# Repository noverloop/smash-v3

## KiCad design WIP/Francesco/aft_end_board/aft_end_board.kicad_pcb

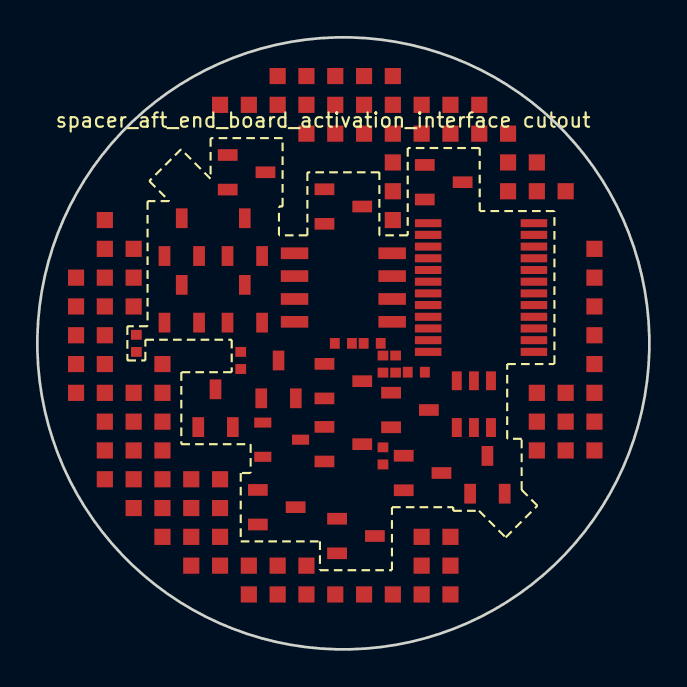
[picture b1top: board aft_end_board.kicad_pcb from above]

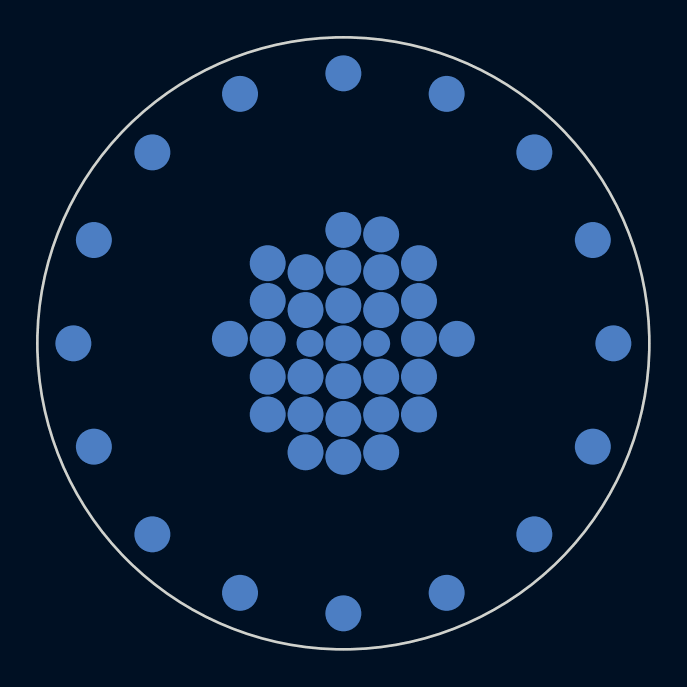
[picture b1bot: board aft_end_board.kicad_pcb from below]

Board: 14 copper layers, 34.0 x 34.0 mm, 77 parts (48 on the bottom side), 71 nets, no tracks yet.

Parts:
C_CAN_GW: C0402 X7R 100nF; Capacitor_SMD_C_0402_1005Metric
J_aft_end_board_spacer_aft_end_board_activation_interface: LGA_lands; J_aft_end_board_spacer_aft_end_board_activation_interface
P_ACT_WIRE_0: P_ACT_WIRE_0; Pogo_Pad_D2.0mm
P_ACT_WIRE_1: P_ACT_WIRE_1; Pogo_Pad_D2.0mm
P_ACT_WIRE_2: P_ACT_WIRE_2; Pogo_Pad_D2.0mm
P_ACT_WIRE_3: P_ACT_WIRE_3; Pogo_Pad_D2.0mm
P_ACT_WIRE_4: P_ACT_WIRE_4; Pogo_Pad_D2.0mm
P_ACT_WIRE_5: P_ACT_WIRE_5; Pogo_Pad_D2.0mm
P_ACT_WIRE_6: P_ACT_WIRE_6; Pogo_Pad_D2.0mm
P_ACT_WIRE_7: P_ACT_WIRE_7; Pogo_Pad_D2.0mm
P_ACT_WIRE_8: P_ACT_WIRE_8; Pogo_Pad_D2.0mm
P_ACT_WIRE_9: P_ACT_WIRE_9; Pogo_Pad_D2.0mm
P_ACT_WIRE_10: P_ACT_WIRE_10; Pogo_Pad_D2.0mm
P_ACT_WIRE_11: P_ACT_WIRE_11; Pogo_Pad_D2.0mm
P_ACT_WIRE_12: P_ACT_WIRE_12; Pogo_Pad_D2.0mm
P_ACT_WIRE_13: P_ACT_WIRE_13; Pogo_Pad_D2.0mm
P_ACT_WIRE_14: P_ACT_WIRE_14; Pogo_Pad_D2.0mm
P_ACT_WIRE_15: P_ACT_WIRE_15; Pogo_Pad_D2.0mm
P_FIRE_COMMON: P_FIRE_COMMON; Pogo_Pad_D2.0mm
Q_FIRE_ARM: DMP6110SVT-7; SOT95P280X100-6N
Q_FIRE_ARM_LS: BSS138LT1G; SOT96P237X111-3N
Q_FIRE_N0, Q_FIRE_N1, Q_FIRE_N2, Q_FIRE_N3, Q_FIRE_N4, Q_FIRE_N5, Q_FIRE_N6, Q_FIRE_N7, Q_FIRE_N8, Q_FIRE_N9, Q_FIRE_N10, Q_FIRE_N11, Q_FIRE_N12, Q_FIRE_N13, Q_FIRE_N14, Q_FIRE_N15: DMN6075SQ-7; SOT96P240X110-3N
R_EXT_CAN_TERM: CRCW0402 120 1% e3; Resistor_SMD_R_0402_1005Metric
R_FIRE_ARM_H: CRCW0402 100k 1% e3; Resistor_SMD_R_0402_1005Metric
R_FIRE_ARM_L: CRCW0402 100k 1% e3; Resistor_SMD_R_0402_1005Metric
R_FIRE_BLEED: CRCW0402 100k 1% e3; Resistor_SMD_R_0402_1005Metric
R_FIRE_MON1: CRCW0402 100k 1% e3; Resistor_SMD_R_0402_1005Metric
R_FIRE_MON2: CRCW0402 11k 1% e3; Resistor_SMD_R_0402_1005Metric
R_JUMP_PAD: CRCW0402 10k 1% e3; Resistor_SMD_R_0402_1005Metric
TP_ACT_CONFIRM: TP_ACT_CONFIRM; Pogo_Pad_D2.0mm
TP_ACT_MOTOR1: TP_ACT_MOTOR1; Pogo_Pad_D2.0mm
TP_ACT_MOTOR2: TP_ACT_MOTOR2; Pogo_Pad_D2.0mm
TP_ACT_MOTOR3: TP_ACT_MOTOR3; Pogo_Pad_D2.0mm
TP_ACT_MOTOR4: TP_ACT_MOTOR4; Pogo_Pad_D2.0mm
TP_ACT_SET: TP_ACT_SET; Pogo_Pad_D2.0mm
TP_BAT_PROT: TP_BAT_PROT; Pogo_Pad_D2.0mm
TP_BAT_RAW: TP_BAT_RAW; Pogo_Pad_D2.0mm
TP_BOOT0: TP_BOOT0; Pogo_Pad_D2.0mm
TP_CAN_N: TP_CAN_N; Pogo_Pad_D2.0mm
TP_CAN_P: TP_CAN_P; Pogo_Pad_D2.0mm
TP_FIN_HALL: TP_FIN_HALL; Pogo_Pad_D2.0mm
TP_FIN_VREF: TP_FIN_VREF; Pogo_Pad_D2.0mm
TP_GND_ACT: TP_GND_ACT; Pogo_Pad_D2.0mm
TP_GPIO_0: TP_GPIO_0; Pogo_Pad_D2.0mm
TP_GPIO_1: TP_GPIO_1; Pogo_Pad_D2.0mm
TP_GPIO_2: TP_GPIO_2; Pogo_Pad_D2.0mm
TP_GPIO_3: TP_GPIO_3; Pogo_Pad_D2.0mm
TP_I2C_SCL: TP_I2C_SCL; Pogo_Pad_D2.0mm
TP_I2C_SDA: TP_I2C_SDA; Pogo_Pad_D2.0mm
TP_JUMP_GND: TP_JUMP_GND; TestPoint_TestPoint_Pad_D1.5mm
TP_JUMP_WAKE: TP_JUMP_WAKE; TestPoint_TestPoint_Pad_D1.5mm
TP_NRST: TP_NRST; Pogo_Pad_D2.0mm
TP_SPI_CS_FIN: TP_SPI_CS_FIN; Pogo_Pad_D2.0mm
TP_SPI_MISO: TP_SPI_MISO; Pogo_Pad_D2.0mm
TP_SPI_MOSI: TP_SPI_MOSI; Pogo_Pad_D2.0mm
TP_SPI_SCLK: TP_SPI_SCLK; Pogo_Pad_D2.0mm
TP_SWCLK: TP_SWCLK; Pogo_Pad_D2.0mm
TP_SWDIO: TP_SWDIO; Pogo_Pad_D2.0mm
TP_SWO: TP_SWO; Pogo_Pad_D2.0mm
TP_VDD: TP_VDD; Pogo_Pad_D2.0mm
U_CAN_GW: TCAN1042GVDQ1; SOIC127P600X175-8N
U_FIRE_DEC: CD74HC4514PW; SOP65P640X120-24N

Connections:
3V3: J_aft_end_board_spacer_aft_end_board_ac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.1, J_aft_end_board_spacer_aft_end_board_ac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.34, J_aft_end_board_spacer_aft_end_board_ac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.40, U_CAN_GW.5
3V3_AON: J_aft_end_board_spacer_aft_end_board_ac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.2, J_aft_end_board_spacer_aft_end_board_ac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.35, TP_VDD.1
ACTIVATE_CONFIRM: J_aft_end_board_spacer_aft_end_board_ac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.3, R_FIRE_MON1.2, R_FIRE_MON2.1, TP_ACT_CONFIRM.1
ACTIVATE_SET: J_aft_end_board_spacer_aft_end_board_ac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.4, Q_FIRE_ARM_LS.1, TP_ACT_SET.1
ACT_WIRE_0: P_ACT_WIRE_0.1, Q_FIRE_N0.3
ACT_WIRE_1: P_ACT_WIRE_1.1, Q_FIRE_N1.3
ACT_WIRE_2: P_ACT_WIRE_2.1, Q_FIRE_N2.3
ACT_WIRE_3: P_ACT_WIRE_3.1, Q_FIRE_N3.3
ACT_WIRE_4: P_ACT_WIRE_4.1, Q_FIRE_N4.3
ACT_WIRE_5: P_ACT_WIRE_5.1, Q_FIRE_N5.3
ACT_WIRE_6: P_ACT_WIRE_6.1, Q_FIRE_N6.3
ACT_WIRE_7: P_ACT_WIRE_7.1, Q_FIRE_N7.3
ACT_WIRE_8: P_ACT_WIRE_8.1, Q_FIRE_N8.3
ACT_WIRE_9: P_ACT_WIRE_9.1, Q_FIRE_N9.3
ACT_WIRE_10: P_ACT_WIRE_10.1, Q_FIRE_N10.3
ACT_WIRE_11: P_ACT_WIRE_11.1, Q_FIRE_N11.3
ACT_WIRE_12: P_ACT_WIRE_12.1, Q_FIRE_N12.3
ACT_WIRE_13: P_ACT_WIRE_13.1, Q_FIRE_N13.3
ACT_WIRE_14: P_ACT_WIRE_14.1, Q_FIRE_N14.3
ACT_WIRE_15: P_ACT_WIRE_15.1, Q_FIRE_N15.3
BAT_PROT: J_aft_end_board_spacer_aft_end_board_ac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.5, J_aft_end_board_spacer_aft_end_board_ac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.36, TP_BAT_PROT.1, U_FIRE_DEC.1, U_FIRE_DEC.24
BAT_RAW: J_aft_end_board_spacer_aft_end_board_ac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.6, J_aft_end_board_spacer_aft_end_board_ac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.37, TP_BAT_RAW.1
BOOT0: J_aft_end_board_spacer_aft_end_board_ac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.7, TP_BOOT0.1
COMP_5V: C_CAN_GW.1, J_aft_end_board_spacer_aft_end_board_ac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.8, J_aft_end_board_spacer_aft_end_board_ac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.38, U_CAN_GW.3
COMP_SWDCLK: J_aft_end_board_spacer_aft_end_board_ac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.9, TP_SWCLK.1
COMP_SWDIO: J_aft_end_board_spacer_aft_end_board_ac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.10, TP_SWDIO.1
EXT_CAN_N: R_EXT_CAN_TERM.2, TP_CAN_N.1, U_CAN_GW.6
EXT_CAN_P: R_EXT_CAN_TERM.1, TP_CAN_P.1, U_CAN_GW.7
EXT_CAN_RX: J_aft_end_board_spacer_aft_end_board_ac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.11, U_CAN_GW.4
EXT_CAN_TX: J_aft_end_board_spacer_aft_end_board_ac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.12, U_CAN_GW.1
FIN1_AOUT1: J_aft_end_board_spacer_aft_end_board_ac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.13, TP_ACT_MOTOR1.1
FIN2_AOUT1: J_aft_end_board_spacer_aft_end_board_ac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.14, TP_ACT_MOTOR2.1
FIN3_AOUT1: J_aft_end_board_spacer_aft_end_board_ac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.15, TP_ACT_MOTOR3.1
FIN4_AOUT1: J_aft_end_board_spacer_aft_end_board_ac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.16, TP_ACT_MOTOR4.1
FIN_HALL: J_aft_end_board_spacer_aft_end_board_ac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.17, TP_FIN_HALL.1
FIN_VREF: J_aft_end_board_spacer_aft_end_board_ac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.18, TP_FIN_VREF.1
FIRE_ARMED: P_FIRE_COMMON.1, Q_FIRE_ARM.1, Q_FIRE_ARM.2, Q_FIRE_ARM.5, Q_FIRE_ARM.6
FIRE_ARM_G: Q_FIRE_ARM.3, R_FIRE_ARM_H.2, R_FIRE_ARM_L.1
FIRE_ARM_GD: Q_FIRE_ARM_LS.3, R_FIRE_ARM_L.2
FIRE_HV: J_aft_end_board_spacer_aft_end_board_ac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.19, J_aft_end_board_spacer_aft_end_board_ac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.39, Q_FIRE_ARM.4, R_FIRE_ARM_H.1, R_FIRE_BLEED.1, R_FIRE_MON1.1
FLEX_GND: C_CAN_GW.2, J_aft_end_board_spacer_aft_end_board_ac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.20, J_aft_end_board_spacer_aft_end_board_ac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.41, J_aft_end_board_spacer_aft_end_board_ac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.42, J_aft_end_board_spacer_aft_end_board_ac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.43, J_aft_end_board_spacer_aft_end_board_ac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.44, J_aft_end_board_spacer_aft_end_board_ac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.45, J_aft_end_board_spacer_aft_end_board_ac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.46, J_aft_end_board_spacer_aft_end_board_ac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.47, J_aft_end_board_spacer_aft_end_board_ac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.48, J_aft_end_board_spacer_aft_end_board_ac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.49, J_aft_end_board_spacer_aft_end_board_ac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.50, J_aft_end_board_spacer_aft_end_board_ac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.51, J_aft_end_board_spacer_aft_end_board_ac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.52, J_aft_end_board_spacer_aft_end_board_ac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.53, J_aft_end_board_spacer_aft_end_board_ac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.54, J_aft_end_board_spacer_aft_end_board_ac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.55, J_aft_end_board_spacer_aft_end_board_ac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.56, J_aft_end_board_spacer_aft_end_board_ac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.57, J_aft_end_board_spacer_aft_end_board_ac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.58, J_aft_end_board_spacer_aft_end_board_ac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.59, J_aft_end_board_spacer_aft_end_board_ac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.60, J_aft_end_board_spacer_aft_end_board_ac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.61, J_aft_end_board_spacer_aft_end_board_ac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.62, J_aft_end_board_spacer_aft_end_board_ac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.63, J_aft_end_board_spacer_aft_end_board_ac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.64, J_aft_end_board_spacer_aft_end_board_ac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.65, J_aft_end_board_spacer_aft_end_board_ac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.66, J_aft_end_board_spacer_aft_end_board_ac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.67, J_aft_end_board_spacer_aft_end_board_ac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.68, J_aft_end_board_spacer_aft_end_board_ac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.69, J_aft_end_board_spacer_aft_end_board_ac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.70, J_aft_end_board_spacer_aft_end_board_ac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.71, J_aft_end_board_spacer_aft_end_board_ac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.72, J_aft_end_board_spacer_aft_end_board_ac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.73, J_aft_end_board_spacer_aft_end_board_ac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.74, J_aft_end_board_spacer_aft_end_board_ac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.75, J_aft_end_board_spacer_aft_end_board_ac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.76, J_aft_end_board_spacer_aft_end_board_ac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.77, J_aft_end_board_spacer_aft_end_board_ac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.78, J_aft_end_board_spacer_aft_end_board_ac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.79, J_aft_end_board_spacer_aft_end_board_ac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.80, J_aft_end_board_spacer_aft_end_board_ac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.81, J_aft_end_board_spacer_aft_end_board_ac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.82, J_aft_end_board_spacer_aft_end_board_ac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.83, J_aft_end_board_spacer_aft_end_board_ac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.84, J_aft_end_board_spacer_aft_end_board_ac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.85, J_aft_end_board_spacer_aft_end_board_ac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.86, J_aft_end_board_spacer_aft_end_board_ac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.87, J_aft_end_board_spacer_aft_end_board_ac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.88, J_aft_end_board_spacer_aft_end_board_ac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.89, J_aft_end_board_spacer_aft_end_board_ac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.90, J_aft_end_board_spacer_aft_end_board_ac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.91, J_aft_end_board_spacer_aft_end_board_ac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.92, J_aft_end_board_spacer_aft_end_board_ac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.93, J_aft_end_board_spacer_aft_end_board_ac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.94, J_aft_end_board_spacer_aft_end_board_ac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.95, J_aft_end_board_spacer_aft_end_board_ac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.96, J_aft_end_board_spacer_aft_end_board_ac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.97, J_aft_end_board_spacer_aft_end_board_ac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.98, Q_FIRE_ARM_LS.2, Q_FIRE_N0.2, Q_FIRE_N1.2, Q_FIRE_N2.2, Q_FIRE_N3.2, Q_FIRE_N4.2, Q_FIRE_N5.2, Q_FIRE_N6.2, Q_FIRE_N7.2, Q_FIRE_N8.2, Q_FIRE_N9.2, Q_FIRE_N10.2, Q_FIRE_N11.2, Q_FIRE_N12.2, Q_FIRE_N13.2, Q_FIRE_N14.2, Q_FIRE_N15.2, R_FIRE_BLEED.2, R_FIRE_MON2.2, TP_GND_ACT.1, TP_JUMP_GND.1, U_CAN_GW.2, U_CAN_GW.8, U_FIRE_DEC.12, U_FIRE_DEC.23
GPIO_EXT_0: J_aft_end_board_spacer_aft_end_board_ac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.21, TP_GPIO_0.1, U_FIRE_DEC.2
GPIO_EXT_1: J_aft_end_board_spacer_aft_end_board_ac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.22, TP_GPIO_1.1, U_FIRE_DEC.3
GPIO_EXT_2: J_aft_end_board_spacer_aft_end_board_ac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.23, TP_GPIO_2.1, U_FIRE_DEC.21
GPIO_EXT_3: J_aft_end_board_spacer_aft_end_board_ac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.24, TP_GPIO_3.1, U_FIRE_DEC.22
JUMP_PAD: R_JUMP_PAD.1, TP_JUMP_WAKE.1
JUMP_WAKE: J_aft_end_board_spacer_aft_end_board_ac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.25, R_JUMP_PAD.2
NRST: J_aft_end_board_spacer_aft_end_board_ac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.26, TP_NRST.1
SWO: J_aft_end_board_spacer_aft_end_board_ac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.27, TP_SWO.1
SYS_I2C_SCL: J_aft_end_board_spacer_aft_end_board_ac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.28, TP_I2C_SCL.1
SYS_I2C_SDA: J_aft_end_board_spacer_aft_end_board_ac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.29, TP_I2C_SDA.1
SYS_SPI_CS_FIN: J_aft_end_board_spacer_aft_end_board_ac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.30, TP_SPI_CS_FIN.1
SYS_SPI_MISO: J_aft_end_board_spacer_aft_end_board_ac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.31, TP_SPI_MISO.1
SYS_SPI_MOSI: J_aft_end_board_spacer_aft_end_board_ac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.32, TP_SPI_MOSI.1
SYS_SPI_SCLK: J_aft_end_board_spacer_aft_end_board_ac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.33, TP_SPI_SCLK.1
Y0_FIRE_SEL: Q_FIRE_N0.1, U_FIRE_DEC.11
Y1_FIRE_SEL: Q_FIRE_N1.1, U_FIRE_DEC.9
Y2_FIRE_SEL: Q_FIRE_N2.1, U_FIRE_DEC.10
Y3_FIRE_SEL: Q_FIRE_N3.1, U_FIRE_DEC.8
Y4_FIRE_SEL: Q_FIRE_N4.1, U_FIRE_DEC.7
Y5_FIRE_SEL: Q_FIRE_N5.1, U_FIRE_DEC.6
Y6_FIRE_SEL: Q_FIRE_N6.1, U_FIRE_DEC.5
Y7_FIRE_SEL: Q_FIRE_N7.1, U_FIRE_DEC.4
Y8_FIRE_SEL: Q_FIRE_N8.1, U_FIRE_DEC.18
Y9_FIRE_SEL: Q_FIRE_N9.1, U_FIRE_DEC.17
Y10_FIRE_SEL: Q_FIRE_N10.1, U_FIRE_DEC.20
Y11_FIRE_SEL: Q_FIRE_N11.1, U_FIRE_DEC.19
Y12_FIRE_SEL: Q_FIRE_N12.1, U_FIRE_DEC.14
Y13_FIRE_SEL: Q_FIRE_N13.1, U_FIRE_DEC.13
Y14_FIRE_SEL: Q_FIRE_N14.1, U_FIRE_DEC.16
Y15_FIRE_SEL: Q_FIRE_N15.1, U_FIRE_DEC.15

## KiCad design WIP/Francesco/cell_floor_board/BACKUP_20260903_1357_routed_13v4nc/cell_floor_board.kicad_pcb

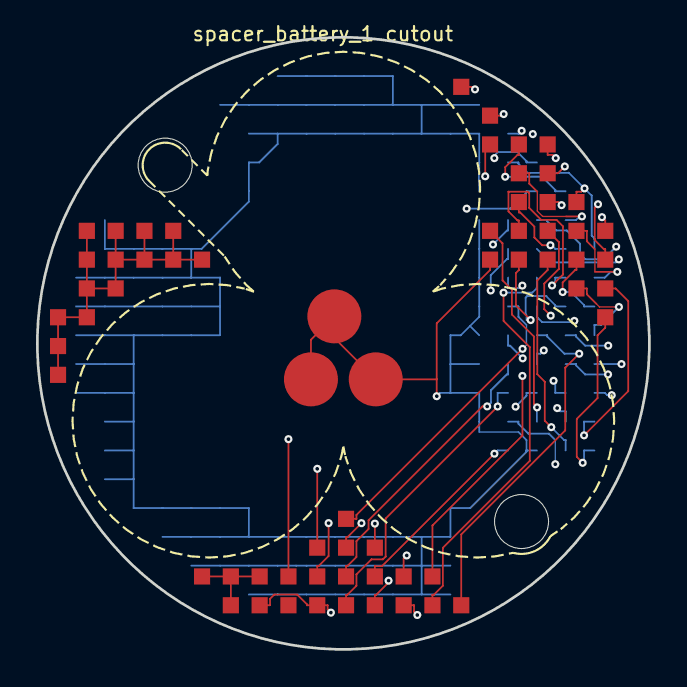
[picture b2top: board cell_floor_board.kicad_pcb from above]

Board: 6 copper layers, 34.0 x 34.0 mm, 7 parts (1 on the bottom side), 35 nets.

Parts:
J_cell_floor_board_spacer_battery_1: LGA_lands; J_cell_floor_board_spacer_battery_1
MECH1, MECH2: smash_mech_potting
P_CELL_TAB_NEG1, P_CELL_TAB_NEG2, P_CELL_TAB_NEG3: CellSolderTab; CellSolderTab_placeholder
P_cell_floor_board_spacer_activation_interface_cell_floor_board: LGA_lands; P_cell_floor_board_spacer_activation_interface_cell_floor_b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

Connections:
3V3: J_cell_floor_board_spacer_battery_1.1, J_cell_floor_board_spacer_battery_1.36, J_cell_floor_board_spacer_battery_1.41, P_cell_floor_board_spacer_activation_in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.1, P_cell_floor_board_spacer_activation_in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.36, P_cell_floor_board_spacer_activation_in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.41
3V3_AON: J_cell_floor_board_spacer_battery_1.2, J_cell_floor_board_spacer_battery_1.37, P_cell_floor_board_spacer_activation_in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.2, P_cell_floor_board_spacer_activation_in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.37
ACTIVATE_CONFIRM: J_cell_floor_board_spacer_battery_1.3, P_cell_floor_board_spacer_activation_in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.3
ACTIVATE_SET: J_cell_floor_board_spacer_battery_1.4, P_cell_floor_board_spacer_activation_in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.4
BAT_PROT: J_cell_floor_board_spacer_battery_1.5, J_cell_floor_board_spacer_battery_1.38, P_cell_floor_board_spacer_activation_in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.5, P_cell_floor_board_spacer_activation_in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.38
BAT_RAW: J_cell_floor_board_spacer_battery_1.6, J_cell_floor_board_spacer_battery_1.39, P_cell_floor_board_spacer_activation_in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.6, P_cell_floor_board_spacer_activation_in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.39
BOOT0: J_cell_floor_board_spacer_battery_1.7, P_cell_floor_board_spacer_activation_in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.7
COMP_5V: J_cell_floor_board_spacer_battery_1.8, J_cell_floor_board_spacer_battery_1.40, P_cell_floor_board_spacer_activation_in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.8, P_cell_floor_board_spacer_activation_in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.40
COMP_SWDCLK: J_cell_floor_board_spacer_battery_1.9, P_cell_floor_board_spacer_activation_in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.9
COMP_SWDIO: J_cell_floor_board_spacer_battery_1.10, P_cell_floor_board_spacer_activation_in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.10
EXT_CAN_RX: J_cell_floor_board_spacer_battery_1.11, P_cell_floor_board_spacer_activation_in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.11
EXT_CAN_TX: J_cell_floor_board_spacer_battery_1.12, P_cell_floor_board_spacer_activation_in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.12
FIN1_AOUT1: J_cell_floor_board_spacer_battery_1.13, P_cell_floor_board_spacer_activation_in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.13
FIN2_AOUT1: J_cell_floor_board_spacer_battery_1.14, P_cell_floor_board_spacer_activation_in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.14
FIN3_AOUT1: J_cell_floor_board_spacer_battery_1.15, P_cell_floor_board_spacer_activation_in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.15
FIN4_AOUT1: J_cell_floor_board_spacer_battery_1.16, P_cell_floor_board_spacer_activation_in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.16
FIN_HALL: J_cell_floor_board_spacer_battery_1.17, P_cell_floor_board_spacer_activation_in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.17
FIN_VREF: J_cell_floor_board_spacer_battery_1.18, P_cell_floor_board_spacer_activation_in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.18
FLEX_GND: J_cell_floor_board_spacer_battery_1.19, J_cell_floor_board_spacer_battery_1.42, J_cell_floor_board_spacer_battery_1.43, J_cell_floor_board_spacer_battery_1.44, J_cell_floor_board_spacer_battery_1.45, J_cell_floor_board_spacer_battery_1.46, J_cell_floor_board_spacer_battery_1.47, J_cell_floor_board_spacer_battery_1.48, J_cell_floor_board_spacer_battery_1.49, J_cell_floor_board_spacer_battery_1.50, J_cell_floor_board_spacer_battery_1.51, J_cell_floor_board_spacer_battery_1.52, J_cell_floor_board_spacer_battery_1.53, J_cell_floor_board_spacer_battery_1.54, J_cell_floor_board_spacer_battery_1.55, J_cell_floor_board_spacer_battery_1.56, J_cell_floor_board_spacer_battery_1.57, J_cell_floor_board_spacer_battery_1.58, J_cell_floor_board_spacer_battery_1.59, J_cell_floor_board_spacer_battery_1.60, P_CELL_TAB_NEG1.1, P_CELL_TAB_NEG2.1, P_CELL_TAB_NEG3.1, P_cell_floor_board_spacer_activation_in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.19, P_cell_floor_board_spacer_activation_in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.42, P_cell_floor_board_spacer_activation_in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.43, P_cell_floor_board_spacer_activation_in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.44, P_cell_floor_board_spacer_activation_in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.45, P_cell_floor_board_spacer_activation_in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.46, P_cell_floor_board_spacer_activation_in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.47, P_cell_floor_board_spacer_activation_in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.48, P_cell_floor_board_spacer_activation_in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.49, P_cell_floor_board_spacer_activation_in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.50, P_cell_floor_board_spacer_activation_in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.51, P_cell_floor_board_spacer_activation_in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.52, P_cell_floor_board_spacer_activation_in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.53, P_cell_floor_board_spacer_activation_in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.54, P_cell_floor_board_spacer_activation_in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.55, P_cell_floor_board_spacer_activation_in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.56, P_cell_floor_board_spacer_activation_in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.57, P_cell_floor_board_spacer_activation_in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.58, P_cell_floor_board_spacer_activation_in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.59, P_cell_floor_board_spacer_activation_in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.60, P_cell_floor_board_spacer_activation_in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.61, P_cell_floor_board_spacer_activation_in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.62, P_cell_floor_board_spacer_activation_in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.63, P_cell_floor_board_spacer_activation_in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.64, P_cell_floor_board_spacer_activation_in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.65, P_cell_floor_board_spacer_activation_in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.66, P_cell_floor_board_spacer_activation_in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.67, P_cell_floor_board_spacer_activation_in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.68, P_cell_floor_board_spacer_activation_in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.69, P_cell_floor_board_spacer_activation_in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.70, P_cell_floor_board_spacer_activation_in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.71, P_cell_floor_board_spacer_activation_in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.72, P_cell_floor_board_spacer_activation_in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.73, P_cell_floor_board_spacer_activation_in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.74, P_cell_floor_board_spacer_activation_in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.75, P_cell_floor_board_spacer_activation_in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.76, P_cell_floor_board_spacer_activation_in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.77, P_cell_floor_board_spacer_activation_in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.78, P_cell_floor_board_spacer_activation_in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.79, P_cell_floor_board_spacer_activation_in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.80, P_cell_floor_board_spacer_activation_in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.81, P_cell_floor_board_spacer_activation_in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.82, P_cell_floor_board_spacer_activation_in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.83, P_cell_floor_board_spacer_activation_in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.84, P_cell_floor_board_spacer_activation_in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.85, P_cell_floor_board_spacer_activation_in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.86, P_cell_floor_board_spacer_activation_in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.87, P_cell_floor_board_spacer_activation_in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.88, P_cell_floor_board_spacer_activation_in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.89, P_cell_floor_board_spacer_activation_in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.90, P_cell_floor_board_spacer_activation_in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.91, P_cell_floor_board_spacer_activation_in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.92, P_cell_floor_board_spacer_activation_in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.93, P_cell_floor_board_spacer_activation_in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.94, P_cell_floor_board_spacer_activation_in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.95, P_cell_floor_board_spacer_activation_in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.96, P_cell_floor_board_spacer_activation_in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.97, P_cell_floor_board_spacer_activation_in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.98, P_cell_floor_board_spacer_activation_in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.99, P_cell_floor_board_spacer_activation_in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.100, P_cell_floor_board_spacer_activation_in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.101, P_cell_floor_board_spacer_activation_in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.102, P_cell_floor_board_spacer_activation_in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.103, P_cell_floor_board_spacer_activation_in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.104, P_cell_floor_board_spacer_activation_in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.105, P_cell_floor_board_spacer_activation_in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.106, P_cell_floor_board_spacer_activation_in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.107, P_cell_floor_board_spacer_activation_in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.108, P_cell_floor_board_spacer_activation_in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.109, P_cell_floor_board_spacer_activation_in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.110, P_cell_floor_board_spacer_activation_in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.111, P_cell_floor_board_spacer_activation_in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.112, P_cell_floor_board_spacer_activation_in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.113, P_cell_floor_board_spacer_activation_in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.114, P_cell_floor_board_spacer_activation_in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.115, P_cell_floor_board_spacer_activation_in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.116, P_cell_floor_board_spacer_activation_in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.117, P_cell_floor_board_spacer_activation_in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.118, P_cell_floor_board_spacer_activation_in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.119, P_cell_floor_board_spacer_activation_in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.120, P_cell_floor_board_spacer_activation_in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.121, P_cell_floor_board_spacer_activation_in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.122, P_cell_floor_board_spacer_activation_in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.123, P_cell_floor_board_spacer_activation_in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.124, P_cell_floor_board_spacer_activation_in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.125, P_cell_floor_board_spacer_activation_in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.126, P_cell_floor_board_spacer_activation_in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.127, P_cell_floor_board_spacer_activation_in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.128, P_cell_floor_board_spacer_activation_in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.129, P_cell_floor_board_spacer_activation_in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.130, P_cell_floor_board_spacer_activation_in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.131, P_cell_floor_board_spacer_activation_in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.132, P_cell_floor_board_spacer_activation_in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.133, P_cell_floor_board_spacer_activation_in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.134, P_cell_floor_board_spacer_activation_in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.135, P_cell_floor_board_spacer_activation_in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.136, P_cell_floor_board_spacer_activation_in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.137, P_cell_floor_board_spacer_activation_in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.138, P_cell_floor_board_spacer_activation_in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.139, P_cell_floor_board_spacer_activation_in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.140, P_cell_floor_board_spacer_activation_in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.141, P_cell_floor_board_spacer_activation_in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.142, P_cell_floor_board_spacer_activation_in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.143, P_cell_floor_board_spacer_activation_in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.144, P_cell_floor_board_spacer_activation_in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.145, P_cell_floor_board_spacer_activation_in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.146, P_cell_floor_board_spacer_activation_in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.147, P_cell_floor_board_spacer_activation_in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.148, P_cell_floor_board_spacer_activation_in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.149, P_cell_floor_board_spacer_activation_in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.150
GPIO_EXT_0: J_cell_floor_board_spacer_battery_1.20, P_cell_floor_board_spacer_activation_in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.20
GPIO_EXT_1: J_cell_floor_board_spacer_battery_1.21, P_cell_floor_board_spacer_activation_in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.21
GPIO_EXT_2: J_cell_floor_board_spacer_battery_1.22, P_cell_floor_board_spacer_activation_in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.22
GPIO_EXT_3: J_cell_floor_board_spacer_battery_1.23, P_cell_floor_board_spacer_activation_in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.23
H3LIS_INT1: J_cell_floor_board_spacer_battery_1.24, P_cell_floor_board_spacer_activation_in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.24
I2C3_SCL: J_cell_floor_board_spacer_battery_1.25, P_cell_floor_board_spacer_activation_in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.25
I2C3_SDA: J_cell_floor_board_spacer_battery_1.26, P_cell_floor_board_spacer_activation_in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.26
JUMP_WAKE: J_cell_floor_board_spacer_battery_1.27, P_cell_floor_board_spacer_activation_in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.27
NRST: J_cell_floor_board_spacer_battery_1.28, P_cell_floor_board_spacer_activation_in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.28
SWO: J_cell_floor_board_spacer_battery_1.29, P_cell_floor_board_spacer_activation_in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.29
SYS_I2C_SCL: J_cell_floor_board_spacer_battery_1.30, P_cell_floor_board_spacer_activation_in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.30
SYS_I2C_SDA: J_cell_floor_board_spacer_battery_1.31, P_cell_floor_board_spacer_activation_in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.31
SYS_SPI_CS_FIN: J_cell_floor_board_spacer_battery_1.32, P_cell_floor_board_spacer_activation_in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.32
SYS_SPI_MISO: J_cell_floor_board_spacer_battery_1.33, P_cell_floor_board_spacer_activation_in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.33
SYS_SPI_MOSI: J_cell_floor_board_spacer_battery_1.34, P_cell_floor_board_spacer_activation_in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.34
SYS_SPI_SCLK: J_cell_floor_board_spacer_battery_1.35, P_cell_floor_board_spacer_activation_in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.35

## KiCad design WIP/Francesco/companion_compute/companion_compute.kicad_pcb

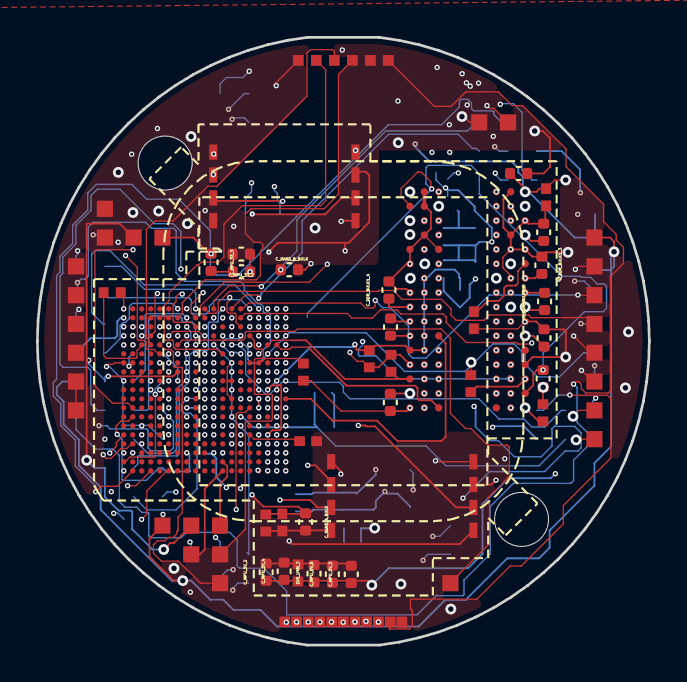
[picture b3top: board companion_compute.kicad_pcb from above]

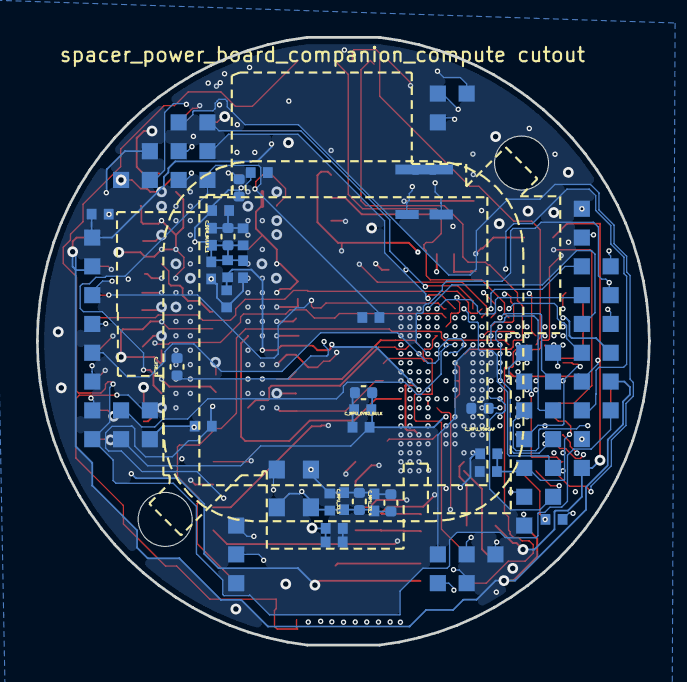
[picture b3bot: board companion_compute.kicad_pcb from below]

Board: 20 copper layers, 34.0 x 33.8 mm, 69 parts (31 on the bottom side), 142 nets.

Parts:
C_DDR_BULK1_1, C_DDR_BULK1_2, C_DDR_BULK1_3, C_DDR_BULK1_4, C_DDR_BULK1_5, C_DDR_BULK2_1, C_DDR_BULK2_2, C_DDR_BULK2_3, C_DDR_BULK2_4, C_DDR_BULK2_5: C-Series MIL-PRF-32535 X7R 0603 2.2uF; C_0402_1005Metric
C_DDR_VDD1, C_DDR_VDD2, C_DDR_VDD3, C_DDR_VDD4, C_DDR_VDD5, C_DDR_VDD6: C0402 X7R 100nF; C_0402_1005Metric
C_DDR_VPP1: C-Series MIL-PRF-32535 X7R 0805 1uF; C_0402_1005Metric
C_DDR_VPP2: C0402 X7R 100nF; C_0402_1005Metric
C_DDR_VREFCA: C0402 X7R 100nF; C_0402_1005Metric
C_MPU_0V82_1, C_MPU_0V82_2, C_MPU_5V2, C_MPU_18A_1, C_MPU_18A_2, C_MPU_33b: C0402 X7R 100nF; C_0402_1005Metric
C_MPU_0V82_BULK, C_MPU_5V_1, C_MPU_5V_2, C_MPU_5V_3, C_MPU_5V_4, C_MPU_5V_5, C_MPU_33_1, C_MPU_33_2, C_MPU_33_3, C_MPU_33_4, C_MPU_33_5: C-Series MIL-PRF-32535 X7R 0603 2.2uF; C_0402_1005Metric
C_MPU_DDR_ZQ: C0402 X7R 0.1uF; C_0402_1005Metric
C_MPU_HSE_VDD: C0402 X7R 100nF; C_0402_1005Metric
C_MPU_LSE_VDD: C0402 X7R 100nF; C_0402_1005Metric
C_MPU_NRST: C0402 X7R 100nF; C_0402_1005Metric
C_MPU_QDDR_1, C_MPU_QDDR_2: C0402 X7R 100nF; C_0402_1005Metric
C_MPU_V08CAP: C-Series MIL-PRF-32535 X7R 0603 2.2uF; C_0402_1005Metric
C_NAND_A_BULK: C-Series MIL-PRF-32535 X7R 0805 1uF; C_0402_1005Metric
C_NAND_A_VCC: C0402 X7R 100nF; C_0402_1005Metric
C_NAND_B_BULK: C-Series MIL-PRF-32535 X7R 0805 1uF; C_0402_1005Metric
C_NAND_B_VCC: C0402 X7R 100nF; C_0402_1005Metric
C_USB_18: C0402 X7R 100nF; C_0402_1005Metric
C_USB_33: C-Series MIL-PRF-32535 X7R 0805 1uF; C_0402_1005Metric
J_FLEXL_companion_compute__camera_module: FLEX_LAUNCH; J_FLEXL_companion_compute__camera_module
J_FLEXL_companion_compute__qpd_module: FLEX_LAUNCH; J_FLEXL_companion_compute__qpd_module
J_companion_compute_spacer_companion_compute_radar_module: LGA_lands; J_companion_compute_spacer_companion_compute_radar_module
P_companion_compute_spacer_power_board_companion_compute: LGA_lands; P_companion_compute_spacer_power_board_companion_compute
R_DDR_ALERTN_PU: CRCW0402 10k 1% e3; R_0402_1005Metric
R_DDR_RESETN_PD: CRCW0402 10k 1% e3; R_0402_1005Metric
R_DDR_VREFCA_BOT: CRCW0402 1k 1% e3; R_0402_1005Metric
R_DDR_VREFCA_TOP: CRCW0402 1k 1% e3; R_0402_1005Metric
R_DDR_ZQ: CRCW0402 240 1% e3; R_0402_1005Metric
R_MPU_BOOT0: CRCW0402 10k 1% e3; R_0402_1005Metric
R_MPU_CSI_REXT: CRCW0402 12k 1% e3; R_0402_1005Metric
R_MPU_NRST: CRCW0402 10k 1% e3; R_0402_1005Metric
R_MPU_TXRTUNE: CRCW0402 200 1% e3; R_0402_1005Metric
R_USB_VBUS_PD: CRCW0402 100k 1% e3; R_0402_1005Metric
U_DDR4: KTDM4G4B626BGIEAT; BGA96C80P9X16_750X1300X100
U_MPU: STM32MP255DAL3
U_NAND_A: MT29F4G01ABAFDWB-IT_F; SON127P800X600X65-8N
U_NAND_B: MT29F4G01ABAFDWB-IT_F; SON127P800X600X65-8N
Y_MPU_HSE: DSC1001CI5-040.0000; DSC1001CI50080000
Y_MPU_LSE: SiT1630AE-S6-DCC-32.768E; SOT-23_5pins

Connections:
3V3: J_FLEXL_companion_compute__qpd_module.1, P_companion_compute_spacer_power_board_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.1, P_companion_compute_spacer_power_board_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.56
ACTIVATE_CONFIRM: P_companion_compute_spacer_power_board_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.2, U_MPU.C10
ACTIVATE_SET: P_companion_compute_spacer_power_board_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.3, U_MPU.B13
AWR_DRDY: J_companion_compute_spacer_companion_co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.1, U_MPU.U8
AWR_FAULT: J_companion_compute_spacer_companion_co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.2, U_MPU.D5
AWR_NRESET: J_companion_compute_spacer_companion_co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.3, U_MPU.D4
AWR_SPI_CLK: J_companion_compute_spacer_companion_co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.4, U_MPU.B10
AWR_SPI_CS: J_companion_compute_spacer_companion_co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.5, U_MPU.A10
AWR_SPI_MISO: J_companion_compute_spacer_companion_co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.6, U_MPU.A14
AWR_SPI_MOSI: J_companion_compute_spacer_companion_co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.7, U_MPU.B14
BAT_FLT: P_companion_compute_spacer_power_board_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.4, U_MPU.F14
BAT_IMON: P_companion_compute_spacer_power_board_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.5, U_MPU.G5
BAT_PGOOD: P_companion_compute_spacer_power_board_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.6, U_MPU.F5
BAT_PROT: J_companion_compute_spacer_companion_co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.8, J_companion_compute_spacer_companion_co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.17, P_companion_compute_spacer_power_board_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.7, P_companion_compute_spacer_power_board_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.57
BOOT0: P_companion_compute_spacer_power_board_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.8, R_MPU_BOOT0.2, U_MPU.T2
CAM_CSI_CLK_N: J_FLEXL_companion_compute__camera_module.1, U_MPU.C2
CAM_CSI_CLK_P: J_FLEXL_companion_compute__camera_module.2, U_MPU.C1
CAM_CSI_D0_N: J_FLEXL_companion_compute__camera_module.3, U_MPU.E1
CAM_CSI_D0_P: J_FLEXL_companion_compute__camera_module.4, U_MPU.E2
CAM_CSI_D1_N: J_FLEXL_companion_compute__camera_module.5, U_MPU.D2
CAM_CSI_D1_P: J_FLEXL_companion_compute__camera_module.6, U_MPU.D1
CAM_EXTCLK: J_FLEXL_companion_compute__camera_module.7, U_MPU.K9
COMP_0V9: P_companion_compute_spacer_power_board_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.10, P_companion_compute_spacer_power_board_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.47, P_companion_compute_spacer_power_board_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.59, U_MPU.B11, U_MPU.E13, U_MPU.G13, U_MPU.J13, U_MPU.L13, U_MPU.M13
COMP_0V82: C_MPU_0V82_1.1, C_MPU_0V82_2.1, C_MPU_0V82_BULK.1, P_companion_compute_spacer_power_board_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.9, P_companion_compute_spacer_power_board_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.58, U_MPU.B1, U_MPU.C6, U_MPU.G10, U_MPU.H11, U_MPU.J1, U_MPU.J10, U_MPU.K11, U_MPU.L10, U_MPU.M11, U_MPU.N8, U_MPU.N10, U_MPU.N14, U_MPU.P11, U_MPU.P13, U_MPU.R10, U_MPU.T14, U_MPU.U12, U_MPU.W16
COMP_1V2: C_DDR_BULK1_1.1, C_DDR_BULK1_2.1, C_DDR_BULK1_3.1, C_DDR_BULK1_4.1, C_DDR_BULK1_5.1, C_DDR_BULK2_1.1, C_DDR_BULK2_2.1, C_DDR_BULK2_3.1, C_DDR_BULK2_4.1, C_DDR_BULK2_5.1, C_DDR_VDD1.1, C_DDR_VDD2.1, C_DDR_VDD3.1, C_DDR_VDD4.1, C_DDR_VDD5.1, C_DDR_VDD6.1, C_MPU_QDDR_1.1, C_MPU_QDDR_2.1, J_FLEXL_companion_compute__camera_module.8, P_companion_compute_spacer_power_board_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.11, P_companion_compute_spacer_power_board_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.60, R_DDR_ALERTN_PU.2, R_DDR_VREFCA_TOP.1, U_DDR4.A1, U_DDR4.A9, U_DDR4.B3, U_DDR4.B9, U_DDR4.C1, U_DDR4.D1, U_DDR4.D9, U_DDR4.F2, U_DDR4.F8, U_DDR4.G1, U_DDR4.G7, U_DDR4.G9, U_DDR4.J1, U_DDR4.J2, U_DDR4.J8, U_DDR4.J9, U_DDR4.L1, U_DDR4.L9, U_DDR4.R1, U_DDR4.T9, U_MPU.F16, U_MPU.J16, U_MPU.L16, U_MPU.M16, U_MPU.P16, U_MPU.T16
COMP_1V8: C_MPU_18A_1.1, C_MPU_18A_2.1, C_USB_18.1, J_FLEXL_companion_compute__camera_module.9, P_companion_compute_spacer_power_board_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.12, P_companion_compute_spacer_power_board_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.61, U_MPU.C5, U_MPU.D3, U_MPU.D16, U_MPU.E15, U_MPU.G6, U_MPU.H6, U_MPU.J4, U_MPU.N5, U_MPU.N6, U_MPU.R13, U_MPU.T13, U_MPU.U2
COMP_2V8: J_FLEXL_companion_compute__camera_module.10, P_companion_compute_spacer_power_board_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.13
COMP_3V3: C_MPU_33_1.1, C_MPU_33_2.1, C_MPU_33_3.1, C_MPU_33_4.1, C_MPU_33_5.1, C_MPU_33b.1, C_MPU_HSE_VDD.1, C_MPU_LSE_VDD.1, C_NAND_A_BULK.1, C_NAND_A_VCC.1, C_NAND_B_BULK.1, C_NAND_B_VCC.1, C_USB_33.1, J_companion_compute_spacer_companion_co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.9, J_companion_compute_spacer_companion_co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.18, P_companion_compute_spacer_power_board_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.14, R_MPU_NRST.1, R_USB_VBUS_PD.1, U_MPU.D6, U_MPU.D10, U_MPU.E6, U_MPU.E10, U_MPU.F8, U_MPU.F10, U_MPU.H8, U_MPU.K8, U_MPU.L6, U_MPU.R6, U_MPU.R14, U_MPU.U11, U_NAND_A.8, U_NAND_B.8, Y_MPU_HSE.1, Y_MPU_HSE.4, Y_MPU_LSE.4
COMP_5V: C_MPU_5V2.1, C_MPU_5V_1.1, C_MPU_5V_2.1, C_MPU_5V_3.1, C_MPU_5V_4.1, C_MPU_5V_5.1, P_companion_compute_spacer_power_board_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.15
COMP_HSE_IN: U_MPU.R1, Y_MPU_HSE.3
COMP_LSE_IN: U_MPU.M2, Y_MPU_LSE.5
COMP_OUT: P_companion_compute_spacer_power_board_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.16, U_MPU.B12
COMP_SWDIO: P_companion_compute_spacer_power_board_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.18, U_MPU.W2
COMP_VPP: C_DDR_VPP1.1, C_DDR_VPP2.1, P_companion_compute_spacer_power_board_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.19, U_DDR4.B1, U_DDR4.R9
CSI_REXT: R_MPU_CSI_REXT.1, U_MPU.E3
DDR4_A0: U_DDR4.P3, U_MPU.E19
DDR4_A1: U_DDR4.P7, U_MPU.G18
DDR4_A2: U_DDR4.R3, U_MPU.N18
DDR4_A3: U_DDR4.N7, U_MPU.M18
DDR4_A4: U_DDR4.N3, U_MPU.K19
DDR4_A5: U_DDR4.P8, U_MPU.F19
DDR4_A6: U_DDR4.P2, U_MPU.P19
DDR4_A7: U_DDR4.R8, U_MPU.G19
DDR4_A8: U_DDR4.R2, U_MPU.M19
DDR4_A9: U_DDR4.R7, U_MPU.P18
DDR4_A10: U_DDR4.M3, U_MPU.H18
DDR4_A11: U_DDR4.T2, U_MPU.H17
DDR4_A12: U_DDR4.M7, U_MPU.R19
DDR4_A13: U_DDR4.T8, U_MPU.H19
DDR4_ACT_N: U_DDR4.L3, U_MPU.L19
DDR4_ALERT_N: R_DDR_ALERTN_PU.1, U_DDR4.P9, U_MPU.H7
DDR4_BA0: U_DDR4.N2, U_MPU.J18
DDR4_BA1: U_DDR4.N8, U_MPU.N19
DDR4_CAS_N_A15: U_DDR4.M8, U_MPU.L18
DDR4_CKE: U_DDR4.K2, U_MPU.F17
DDR4_CK_C: U_DDR4.K8, U_MPU.L17
DDR4_CK_T: U_DDR4.K7, U_MPU.M17
DDR4_CS_N: U_DDR4.L7, U_MPU.J17
DDR4_DM0_N: U_DDR4.E7, U_MPU.T17
DDR4_DM1_N: U_DDR4.E2, U_MPU.C19
DDR4_DQ0: U_DDR4.F7, U_MPU.W18
DDR4_DQ1: U_DDR4.H8, U_MPU.W17
DDR4_DQ2: U_DDR4.H7, U_MPU.V17
DDR4_DQ3: U_DDR4.J7, U_MPU.U17
DDR4_DQ4: U_DDR4.J3, U_MPU.T19
DDR4_DQ5: U_DDR4.H2, U_MPU.T18
DDR4_DQ6: U_DDR4.H3, U_MPU.U19
DDR4_DQ7: U_DDR4.G2, U_MPU.U18
DDR4_DQ8: U_DDR4.D7, U_MPU.C17
DDR4_DQ9: U_DDR4.B8, U_MPU.A18
DDR4_DQ10: U_DDR4.C7, U_MPU.B17
DDR4_DQ11: U_DDR4.C8, U_MPU.A17
DDR4_DQ12: U_DDR4.C3, U_MPU.D19
DDR4_DQ13: U_DDR4.D3, U_MPU.D18
DDR4_DQ14: U_DDR4.C2, U_MPU.D17
DDR4_DQ15: U_DDR4.A3, U_MPU.C18
DDR4_DQS0_C: U_DDR4.F3, U_MPU.V18
DDR4_DQS0_T: U_DDR4.G3, U_MPU.V19
DDR4_DQS1_C: U_DDR4.A7, U_MPU.B18
DDR4_DQS1_T: U_DDR4.B7, U_MPU.B19
DDR4_ODT: U_DDR4.K3, U_MPU.J19
DDR4_PAR: U_DDR4.T3, U_MPU.E18
DDR4_RAS_N_A16: U_DDR4.L8, U_MPU.F18
DDR4_RESET_N: R_DDR_RESETN_PD.1, U_DDR4.P1, U_MPU.E17
DDR4_VREFCA: C_DDR_VREFCA.1, R_DDR_VREFCA_BOT.1, R_DDR_VREFCA_TOP.2, U_DDR4.M1, U_DDR4.M2, U_MPU.K17, U_MPU.R17
DDR4_WE_N_A14: U_DDR4.L2, U_MPU.K18
DDR4_ZQ_CAL: R_DDR_ZQ.1, U_DDR4.F9
EXT_CAN_RX: P_companion_compute_spacer_power_board_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.20, U_MPU.A13
EXT_CAN_TX: P_companion_compute_spacer_power_board_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.21, U_MPU.A11
FLEX_GND: C_DDR_BULK1_1.2, C_DDR_BULK1_2.2, C_DDR_BULK1_3.2, C_DDR_BULK1_4.2, C_DDR_BULK1_5.2, C_DDR_BULK2_1.2, C_DDR_BULK2_2.2, C_DDR_BULK2_3.2, C_DDR_BULK2_4.2, C_DDR_BULK2_5.2, C_DDR_VDD1.2, C_DDR_VDD2.2, C_DDR_VDD3.2, C_DDR_VDD4.2, C_DDR_VDD5.2, C_DDR_VDD6.2, C_DDR_VPP1.2, C_DDR_VPP2.2, C_DDR_VREFCA.2, C_MPU_0V82_1.2, C_MPU_0V82_2.2, C_MPU_0V82_BULK.2, C_MPU_5V2.2, C_MPU_5V_1.2, C_MPU_5V_2.2, C_MPU_5V_3.2, C_MPU_5V_4.2, C_MPU_5V_5.2, C_MPU_18A_1.2, C_MPU_18A_2.2, C_MPU_33_1.2, C_MPU_33_2.2, C_MPU_33_3.2, C_MPU_33_4.2, C_MPU_33_5.2, C_MPU_33b.2, C_MPU_DDR_ZQ.2, C_MPU_HSE_VDD.2, C_MPU_LSE_VDD.2, C_MPU_NRST.2, C_MPU_QDDR_1.2, C_MPU_QDDR_2.2, C_MPU_V08CAP.2, C_NAND_A_BULK.2, C_NAND_A_VCC.2, C_NAND_B_BULK.2, C_NAND_B_VCC.2, C_USB_18.2, C_USB_33.2, J_FLEXL_companion_compute__camera_module.11, J_FLEXL_companion_compute__qpd_module.2, J_companion_compute_spacer_companion_co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.10, J_companion_compute_spacer_companion_co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.20, J_companion_compute_spacer_companion_co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.21, J_companion_compute_spacer_companion_co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.22, J_companion_compute_spacer_companion_co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.23, J_companion_compute_spacer_companion_co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.24, J_companion_compute_spacer_companion_co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.25, J_companion_compute_spacer_companion_co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.26, J_companion_compute_spacer_companion_co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.27, P_companion_compute_spacer_power_board_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.22, R_DDR_RESETN_PD.2, R_DDR_VREFCA_BOT.2, R_DDR_ZQ.2, R_MPU_BOOT0.1, R_MPU_CSI_REXT.2, R_MPU_TXRTUNE.2, U_DDR4.A2, U_DDR4.A8, U_DDR4.B2, U_DDR4.C9, U_DDR4.D2, U_DDR4.D8, U_DDR4.E1, U_DDR4.E3, U_DDR4.E8, U_DDR4.E9, U_DDR4.F1, U_DDR4.G8, U_DDR4.H1, U_DDR4.H9, U_DDR4.K1, U_DDR4.K9, U_DDR4.M9, U_DDR4.N1, U_DDR4.N9, U_DDR4.T1, U_MPU.A1, U_MPU.A19, U_MPU.C3, U_MPU.C7, U_MPU.D13, U_MPU.E8, U_MPU.E16, U_MPU.F6, U_MPU.F11, U_MPU.F13, U_MPU.G8, U_MPU.G11, U_MPU.H10, U_MPU.H13, U_MPU.H16, U_MPU.J6, U_MPU.J8, U_MPU.J11, U_MPU.J14, U_MPU.K4, U_MPU.K5, U_MPU.K10, U_MPU.K13, U_MPU.K16, U_MPU.L8, U_MPU.L11, U_MPU.M6, U_MPU.M10, U_MPU.N11, U_MPU.N13, U_MPU.N16, U_MPU.P3, U_MPU.P6, U_MPU.P8, U_MPU.P10, U_MPU.P14, U_MPU.R3, U_MPU.R11, U_MPU.R16, U_MPU.R18, U_MPU.T3, U_MPU.U1, U_MPU.W1, U_MPU.W19, U_NAND_A.4, U_NAND_B.4, Y_MPU_HSE.2, Y_MPU_LSE.1, Y_MPU_LSE.2, Y_MPU_LSE.3
GPIO_EXT_0: P_companion_compute_spacer_power_board_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.23, U_MPU.D7
GPIO_EXT_1: P_companion_compute_spacer_power_board_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.24, U_MPU.D8
GPIO_EXT_2: P_companion_compute_spacer_power_board_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.25, U_MPU.D9
GPIO_EXT_3: P_companion_compute_spacer_power_board_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.26, U_MPU.E11
I2C2_SCL: P_companion_compute_spacer_power_board_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.27, U_MPU.B9
I2C2_SDA: P_companion_compute_spacer_power_board_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.28, U_MPU.C9
I2C3_SCL: P_companion_compute_spacer_power_board_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.29, U_MPU.L15
I2C3_SDA: P_companion_compute_spacer_power_board_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.30, U_MPU.L14
IMU1_INT: P_companion_compute_spacer_power_board_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.31, U_MPU.C14
IMU2_INT: P_companion_compute_spacer_power_board_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.32, U_MPU.C15
IMU3_INT: P_companion_compute_spacer_power_board_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.33, U_MPU.D12
MAG_DRDY: P_companion_compute_spacer_power_board_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.34, U_MPU.C13
MPU_DDR_ZQ: C_MPU_DDR_ZQ.1, U_MPU.G16
NAND_OSPI_CLK: U_MPU.G9, U_NAND_A.6, U_NAND_B.6
NAND_OSPI_CS0: U_MPU.E14, U_NAND_A.1
NAND_OSPI_CS1: U_MPU.F15, U_NAND_B.1
NAND_OSPI_IO0: U_MPU.D14, U_NAND_A.5, U_NAND_B.5
NAND_OSPI_IO1: U_MPU.C16, U_NAND_A.2, U_NAND_B.2
NAND_OSPI_IO2: U_MPU.B16, U_NAND_A.3, U_NAND_B.3
NAND_OSPI_IO3: U_MPU.B15, U_NAND_A.7, U_NAND_B.7
NOSE_LED_G: J_companion_compute_spacer_companion_co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.11, U_MPU.E7
NOSE_LED_R: J_companion_compute_spacer_companion_co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.12, U_MPU.E5
NRST: C_MPU_NRST.1, P_companion_compute_spacer_power_board_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.35, R_MPU_NRST.2, U_MPU.N2
PMIC_PWR_OK: P_companion_compute_spacer_power_board_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.36, U_MPU.G1
PWR_HOLD: P_companion_compute_spacer_power_board_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.37, U_MPU.C11
QPD_TIA_A: J_FLEXL_companion_compute__qpd_module.3, U_MPU.B7
QPD_TIA_B: J_FLEXL_companion_compute__qpd_module.4, U_MPU.E4
QPD_TIA_C: J_FLEXL_companion_compute__qpd_module.5, U_MPU.F12
QPD_TIA_D: J_FLEXL_companion_compute__qpd_module.6, U_MPU.F7
RADAR_EN: J_companion_compute_spacer_companion_co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.13, U_MPU.D15
SWO: P_companion_compute_spacer_power_board_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.38, U_MPU.V1
SYS_I2C_SCL: P_companion_compute_spacer_power_board_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.39, U_MPU.J7
SYS_I2C_SDA: P_companion_compute_spacer_power_board_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.40, U_MPU.J9
SYS_SPI_CS_FIN: P_companion_compute_spacer_power_board_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.41, U_MPU.A12
SYS_SPI_MISO: P_companion_compute_spacer_power_board_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.42, U_MPU.C8
SYS_SPI_MOSI: P_companion_compute_spacer_power_board_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.43, U_MPU.E9
SYS_SPI_SCLK: P_companion_compute_spacer_power_board_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.44, U_MPU.B8
TMP1_ALERT: P_companion_compute_spacer_power_board_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.17, P_companion_compute_spacer_power_board_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.45, U_MPU.F9, U_MPU.W4
USB_DM: J_companion_compute_spacer_companion_co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.14, U_MPU.V12
USB_DP: J_companion_compute_spacer_companion_co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.15, U_MPU.W12
USB_TXRTUNE: R_MPU_TXRTUNE.1, U_MPU.R15
USB_VBUS: J_companion_compute_spacer_companion_co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.16, J_companion_compute_spacer_companion_co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.19, P_companion_compute_spacer_power_board_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.46
USB_VBUS_DET: R_USB_VBUS_PD.2, U_MPU.W6
V08_CAP: C_MPU_V08CAP.1, U_MPU.M8
WBA_HCI_IRQ: P_companion_compute_spacer_power_board_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.48, U_MPU.A8
WBA_HCI_MISO: P_companion_compute_spacer_power_board_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.49, U_MPU.E12
WBA_HCI_MOSI: P_companion_compute_spacer_power_board_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.50, U_MPU.A7
WBA_HCI_NSS: P_companion_compute_spacer_power_board_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.51, U_MPU.A16
WBA_HCI_SCK: P_companion_compute_spacer_power_board_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.52, U_MPU.A15
WBA_RST_CMD: P_companion_compute_spacer_power_board_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.53, U_MPU.A9
WBA_UART_RX: P_companion_compute_spacer_power_board_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.54, U_MPU.P12
WBA_UART_TX: P_companion_compute_spacer_power_board_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.55, U_MPU.M15
